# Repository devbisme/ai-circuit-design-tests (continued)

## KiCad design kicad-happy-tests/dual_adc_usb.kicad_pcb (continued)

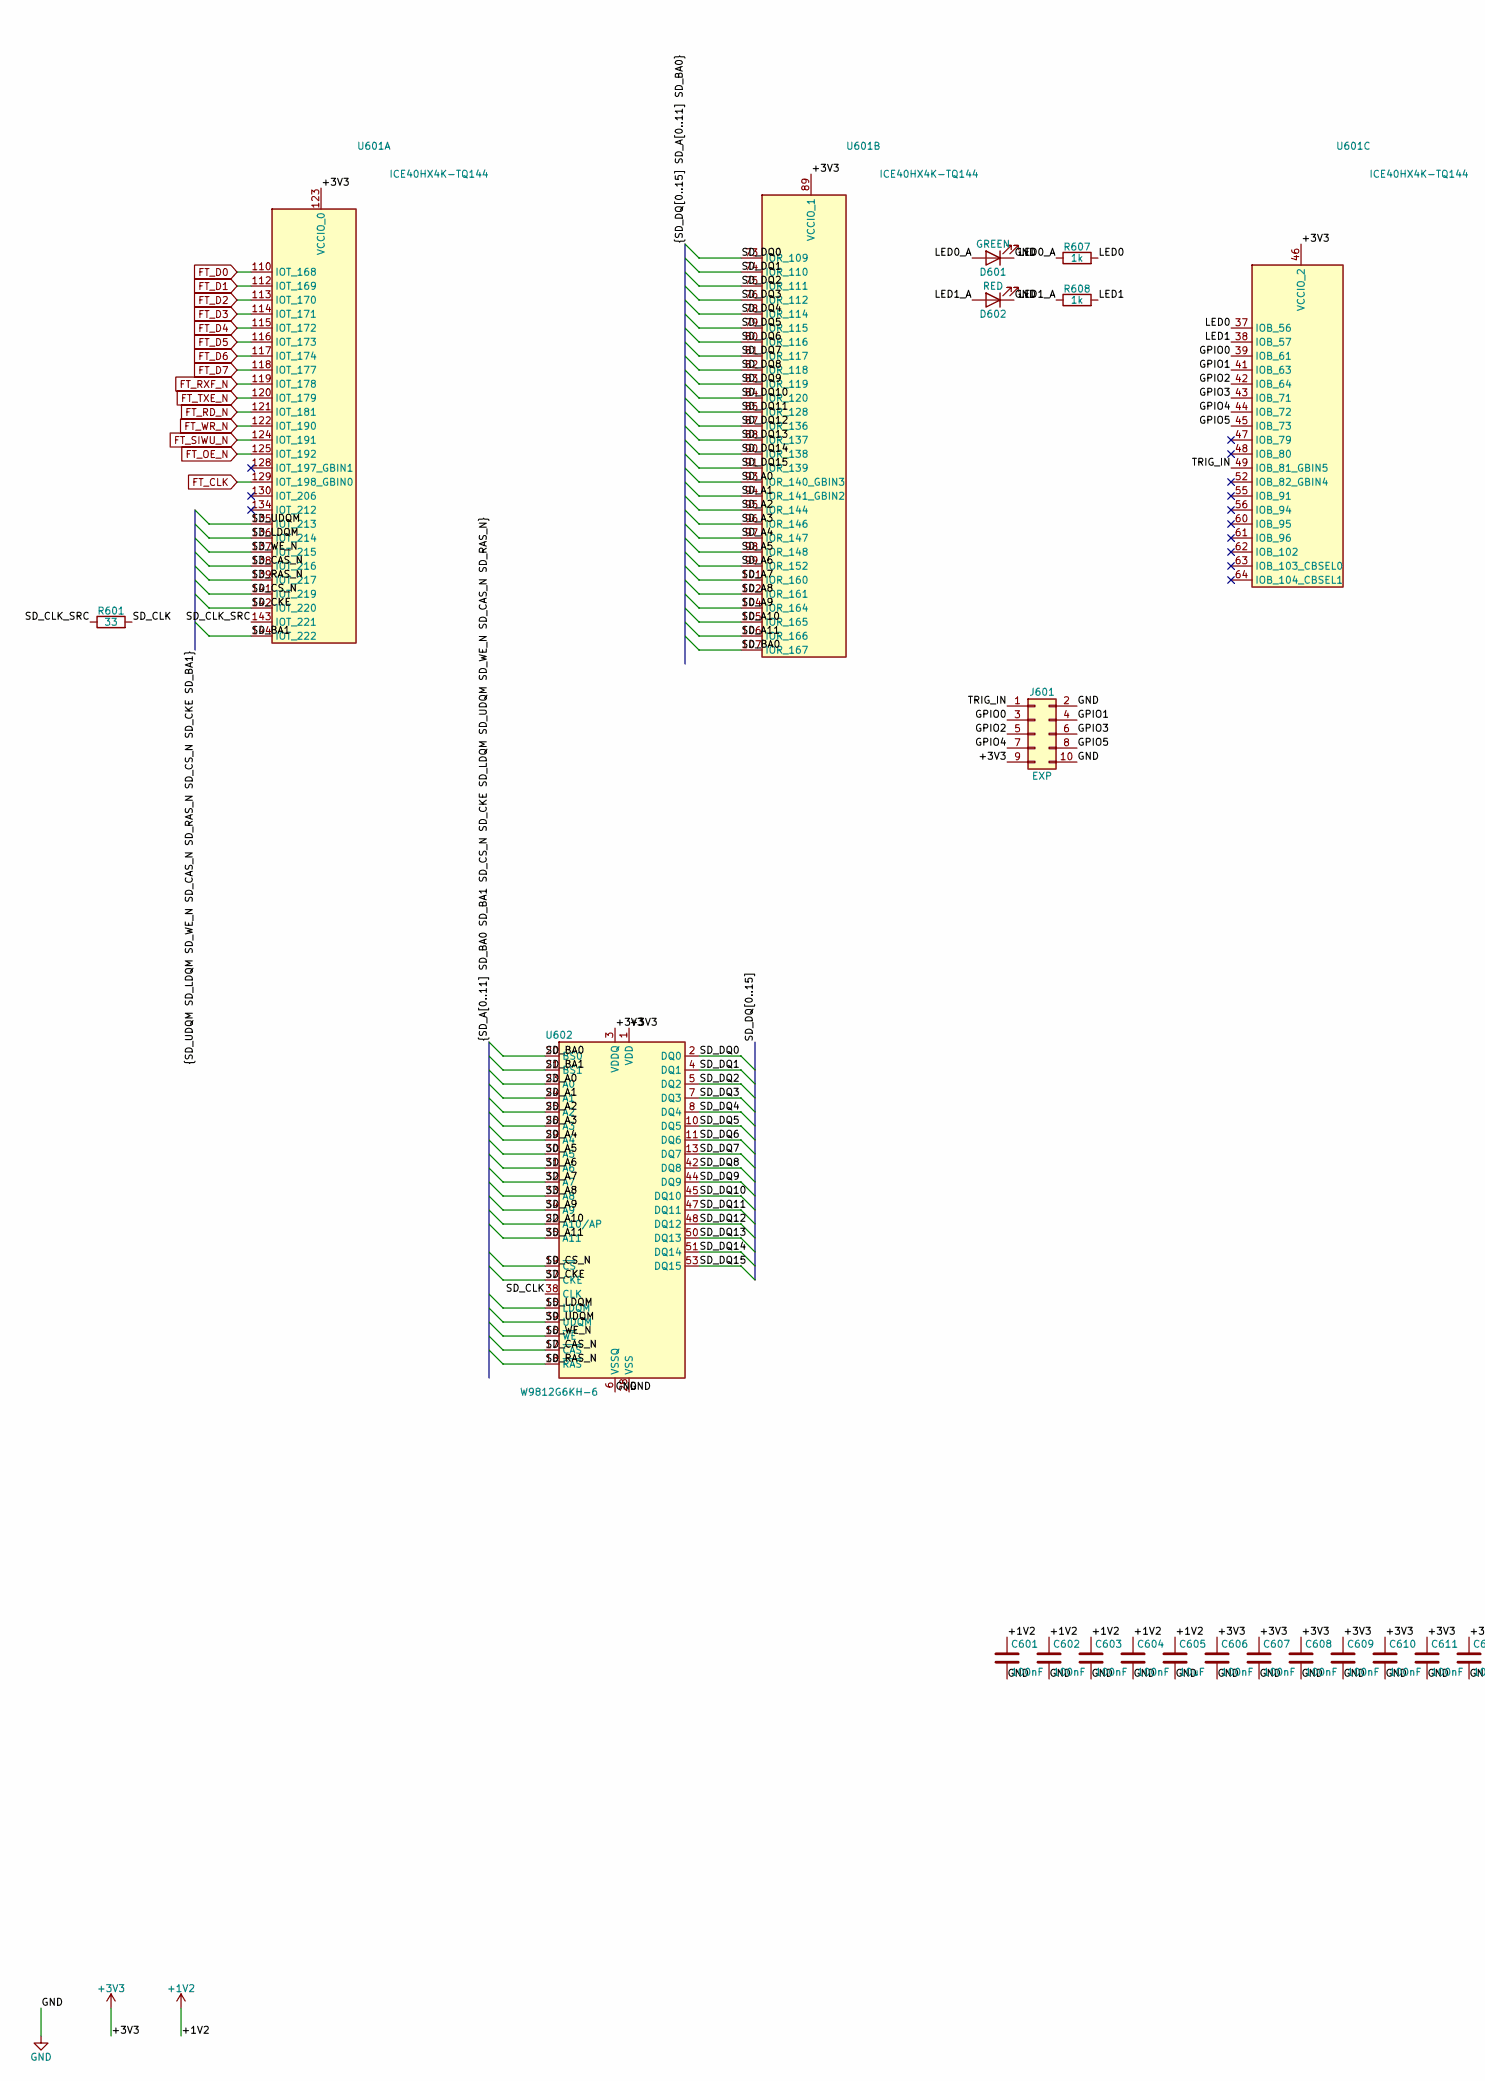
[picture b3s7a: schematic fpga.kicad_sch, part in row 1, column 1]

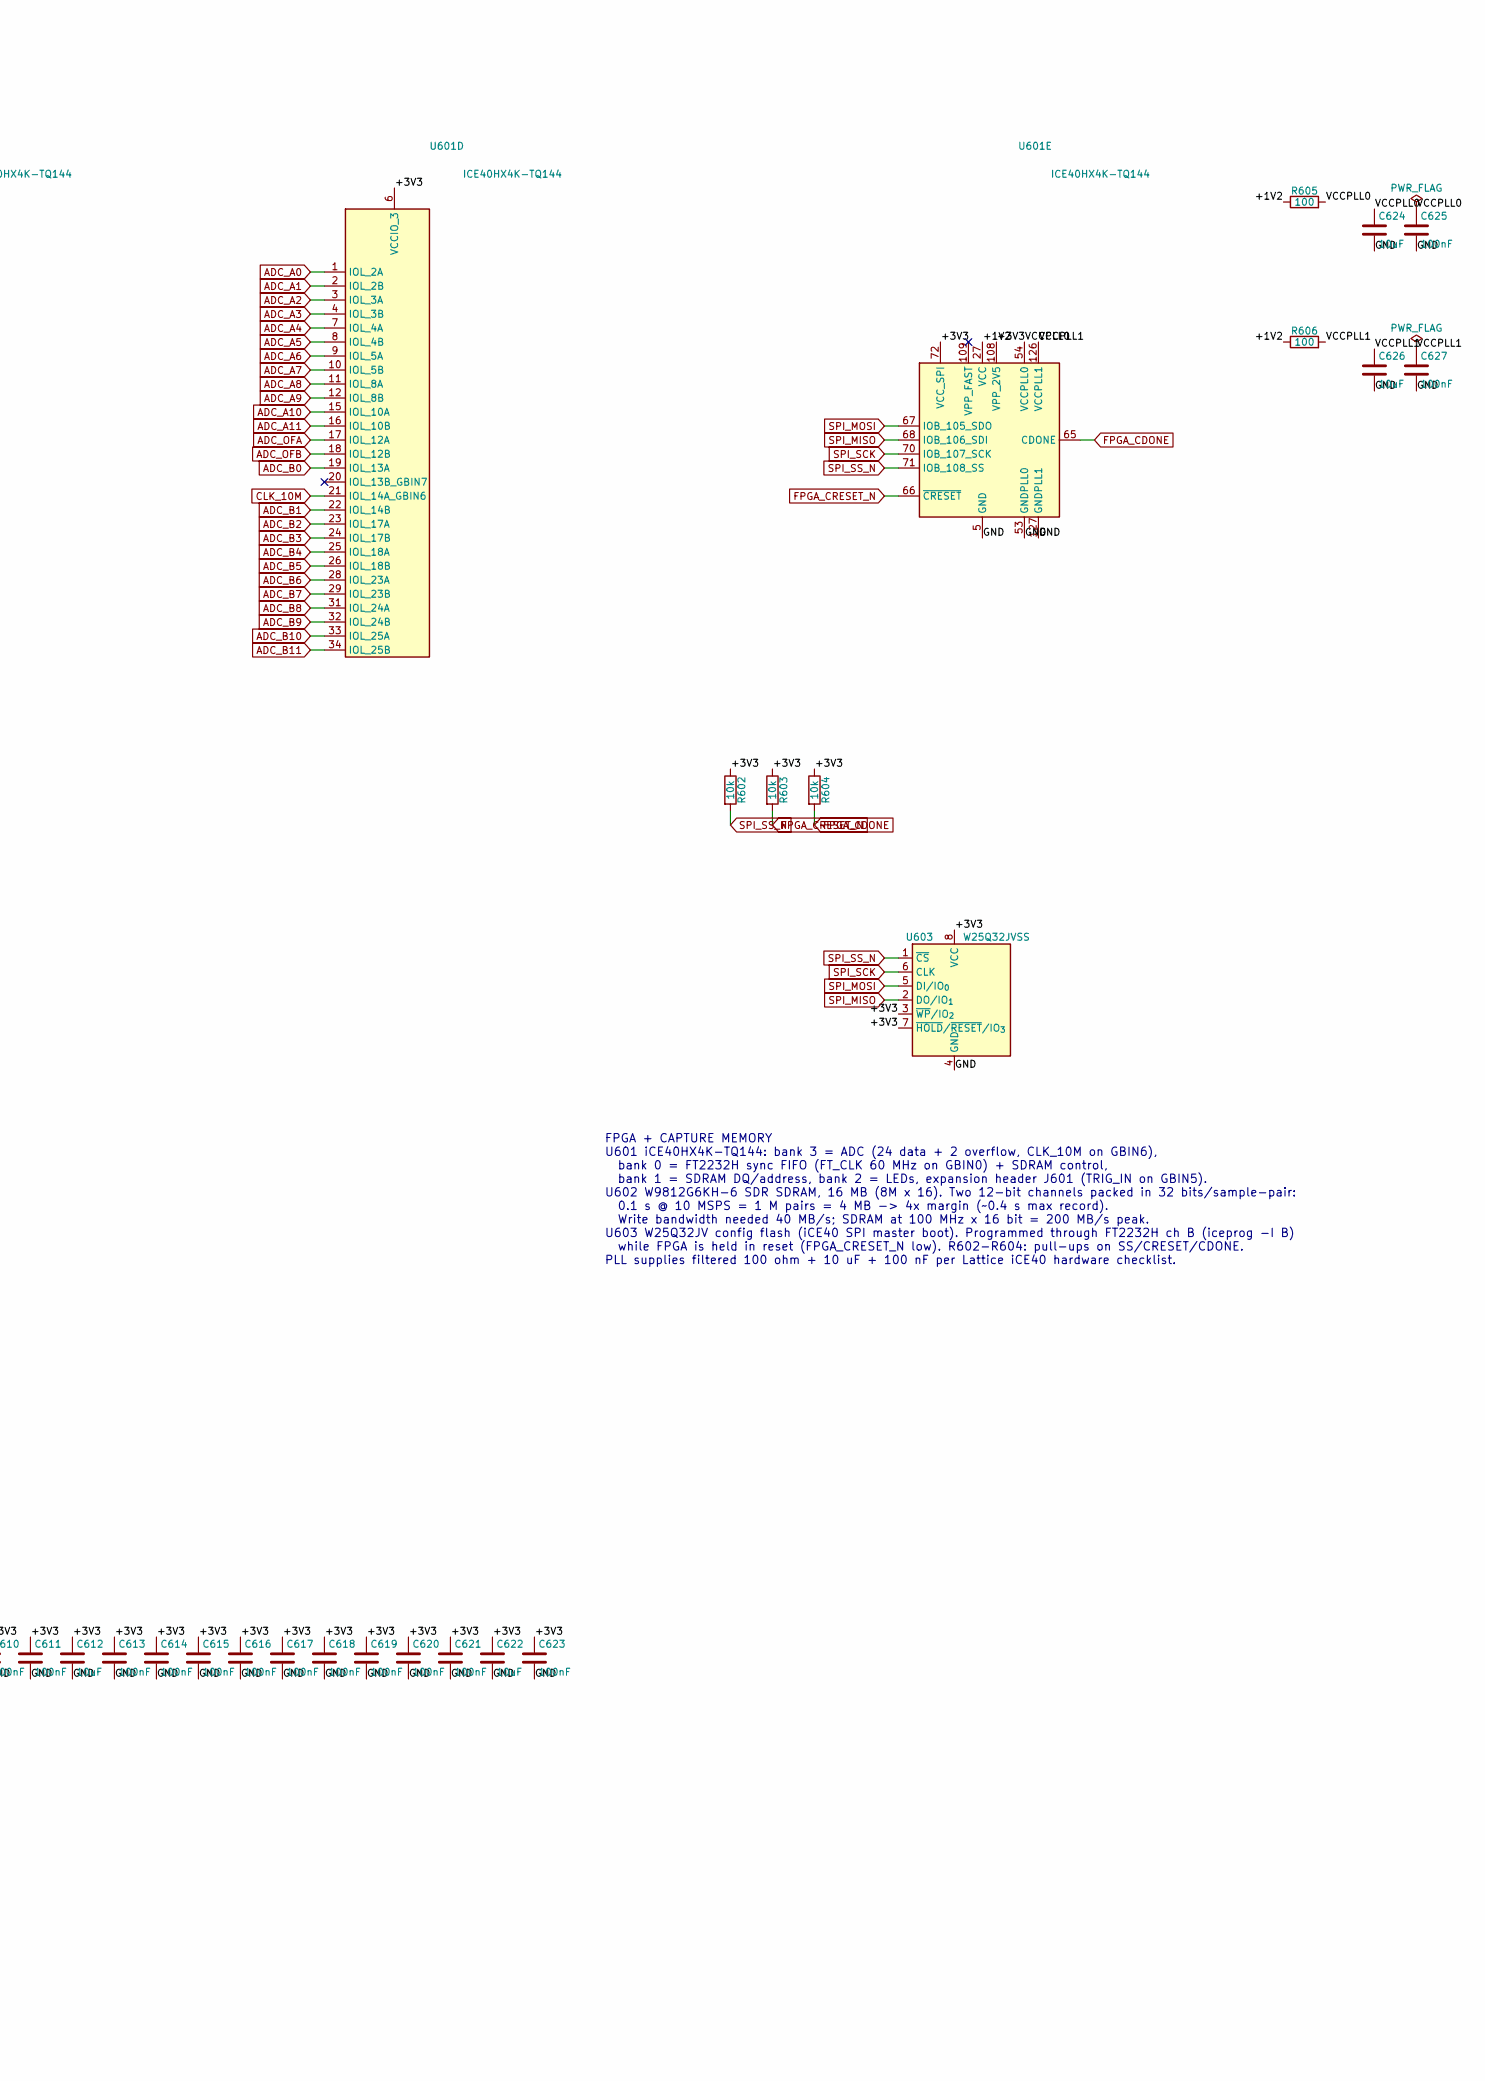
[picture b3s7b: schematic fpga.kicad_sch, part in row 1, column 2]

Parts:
C601, C602, C603, C604, C606, C607, C608, C609, C610, C611, C613, C614, C615, C616, C617, C618, C619, C620, C621, C623, C625, C627: 100nF; C_0402_1005Metric
C605, C612, C622, C624, C626: 10uF; C_0805_2012Metric
D601: GREEN; LED_0603_1608Metric
D602: RED; LED_0603_1608Metric
J601: EXP; PinHeader_2x05_P2.54mm_Vertical
R601: 33; R_0402_1005Metric
R602, R603, R604: 10k; R_0402_1005Metric
R605, R606: 100; R_0402_1005Metric
R607, R608: 1k; R_0402_1005Metric
U601: ICE40HX4K-TQ144; TQFP-144_20x20mm_P0.5mm
U602: W9812G6KH-6; TSOP-II-54_22.2x10.16mm_P0.8mm
U603: W25Q32JVSS; SOIC-8_5.3x5.3mm_P1.27mm

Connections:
+1V2: C601.1, C602.1, C603.1, C604.1, C605.1, R605.1, R606.1, U601.27 (VCC), U601.40 (VCC), U601.92 (VCC), U601.111 (VCC); also elsewhere on the board
+3V3: C606.1, C607.1, C608.1, C609.1, C610.1, C611.1, C612.1, C613.1, C614.1, C615.1, C616.1, C617.1, C618.1, C619.1, C620.1, C621.1, C622.1, C623.1, J601.9, R602.1, R603.1, R604.1, U601.6 (VCCIO_3), U601.30 (VCCIO_3), U601.46 (VCCIO_2), U601.57 (VCCIO_2), U601.72 (VCC_SPI), U601.89 (VCCIO_1), U601.100 (VCCIO_1), U601.108 (VPP_2V5), U601.123 (VCCIO_0), U601.131 (VCCIO_0), U602.1 (VDD), U602.3 (VDDQ), U602.9 (VDDQ), U602.14 (VDD), U602.27 (VDD), U602.43 (VDDQ), U602.49 (VDDQ), U603.3 (~WP/IO_{2}), U603.7 (~HOLD/~RESET/IO_{3}), U603.8 (VCC); also elsewhere on the board
/FPGA_SDRAM/GPIO0: J601.3, U601.39 (IOB_61)
/FPGA_SDRAM/GPIO1: J601.4, U601.41 (IOB_63)
/FPGA_SDRAM/GPIO2: J601.5, U601.42 (IOB_64)
/FPGA_SDRAM/GPIO3: J601.6, U601.43 (IOB_71)
/FPGA_SDRAM/GPIO4: J601.7, U601.44 (IOB_72)
/FPGA_SDRAM/GPIO5: J601.8, U601.45 (IOB_73)
/FPGA_SDRAM/LED0: R607.2, U601.37 (IOB_56)
/FPGA_SDRAM/LED0_A: D601.2 (A), R607.1
/FPGA_SDRAM/LED1: R608.2, U601.38 (IOB_57)
/FPGA_SDRAM/LED1_A: D602.2 (A), R608.1
/FPGA_SDRAM/SD_A0: U601.93 (IOR_140_GBIN3), U602.23 (A0)
/FPGA_SDRAM/SD_A1: U601.94 (IOR_141_GBIN2), U602.24 (A1)
/FPGA_SDRAM/SD_A2: U601.95 (IOR_144), U602.25 (A2)
/FPGA_SDRAM/SD_A3: U601.96 (IOR_146), U602.26 (A3)
/FPGA_SDRAM/SD_A4: U601.97 (IOR_147), U602.29 (A4)
/FPGA_SDRAM/SD_A5: U601.98 (IOR_148), U602.30 (A5)
/FPGA_SDRAM/SD_A6: U601.99 (IOR_152), U602.31 (A6)
/FPGA_SDRAM/SD_A7: U601.101 (IOR_160), U602.32 (A7)
/FPGA_SDRAM/SD_A8: U601.102 (IOR_161), U602.33 (A8)
/FPGA_SDRAM/SD_A9: U601.104 (IOR_164), U602.34 (A9)
/FPGA_SDRAM/SD_A10: U601.105 (IOR_165), U602.22 (A10/AP)
/FPGA_SDRAM/SD_A11: U601.106 (IOR_166), U602.35 (A11)
/FPGA_SDRAM/SD_BA0: U601.107 (IOR_167), U602.20 (BS0)
/FPGA_SDRAM/SD_BA1: U601.144 (IOT_222), U602.21 (BS1)
/FPGA_SDRAM/SD_CAS_N: U601.138 (IOT_216), U602.17 (~CAS)
/FPGA_SDRAM/SD_CKE: U601.142 (IOT_220), U602.37 (CKE)
/FPGA_SDRAM/SD_CLK: R601.2, U602.38 (CLK)
/FPGA_SDRAM/SD_CLK_SRC: R601.1, U601.143 (IOT_221)
/FPGA_SDRAM/SD_CS_N: U601.141 (IOT_219), U602.19 (~CS)
/FPGA_SDRAM/SD_DQ0: U601.73 (IOR_109), U602.2 (DQ0)
/FPGA_SDRAM/SD_DQ1: U601.74 (IOR_110), U602.4 (DQ1)
/FPGA_SDRAM/SD_DQ2: U601.75 (IOR_111), U602.5 (DQ2)
/FPGA_SDRAM/SD_DQ3: U601.76 (IOR_112), U602.7 (DQ3)
/FPGA_SDRAM/SD_DQ4: U601.78 (IOR_114), U602.8 (DQ4)
/FPGA_SDRAM/SD_DQ5: U601.79 (IOR_115), U602.10 (DQ5)
/FPGA_SDRAM/SD_DQ6: U601.80 (IOR_116), U602.11 (DQ6)
/FPGA_SDRAM/SD_DQ7: U601.81 (IOR_117), U602.13 (DQ7)
/FPGA_SDRAM/SD_DQ8: U601.82 (IOR_118), U602.42 (DQ8)
/FPGA_SDRAM/SD_DQ9: U601.83 (IOR_119), U602.44 (DQ9)
/FPGA_SDRAM/SD_DQ10: U601.84 (IOR_120), U602.45 (DQ10)
/FPGA_SDRAM/SD_DQ11: U601.85 (IOR_128), U602.47 (DQ11)
/FPGA_SDRAM/SD_DQ12: U601.87 (IOR_136), U602.48 (DQ12)
/FPGA_SDRAM/SD_DQ13: U601.88 (IOR_137), U602.50 (DQ13)
/FPGA_SDRAM/SD_DQ14: U601.90 (IOR_138), U602.51 (DQ14)
/FPGA_SDRAM/SD_DQ15: U601.91 (IOR_139), U602.53 (DQ15)
/FPGA_SDRAM/SD_LDQM: U601.136 (IOT_214), U602.15 (LDQM)
/FPGA_SDRAM/SD_RAS_N: U601.139 (IOT_217), U602.18 (~RAS)
/FPGA_SDRAM/SD_UDQM: U601.135 (IOT_213), U602.39 (UDQM)
/FPGA_SDRAM/SD_WE_N: U601.137 (IOT_215), U602.16 (~WE)
/FPGA_SDRAM/TRIG_IN: J601.1, U601.49 (IOB_81_GBIN5)
ADC_A0: U601.1 (IOL_2A); also elsewhere on the board
ADC_A1: U601.2 (IOL_2B); also elsewhere on the board
ADC_A2: U601.3 (IOL_3A); also elsewhere on the board
ADC_A3: U601.4 (IOL_3B); also elsewhere on the board
ADC_A4: U601.7 (IOL_4A); also elsewhere on the board
ADC_A5: U601.8 (IOL_4B); also elsewhere on the board
ADC_A6: U601.9 (IOL_5A); also elsewhere on the board
ADC_A7: U601.10 (IOL_5B); also elsewhere on the board
ADC_A8: U601.11 (IOL_8A); also elsewhere on the board
ADC_A9: U601.12 (IOL_8B); also elsewhere on the board
ADC_A10: U601.15 (IOL_10A); also elsewhere on the board
ADC_A11: U601.16 (IOL_10B); also elsewhere on the board
ADC_B0: U601.19 (IOL_13A); also elsewhere on the board
ADC_B1: U601.22 (IOL_14B); also elsewhere on the board
ADC_B2: U601.23 (IOL_17A); also elsewhere on the board
ADC_B3: U601.24 (IOL_17B); also elsewhere on the board
ADC_B4: U601.25 (IOL_18A); also elsewhere on the board
ADC_B5: U601.26 (IOL_18B); also elsewhere on the board
ADC_B6: U601.28 (IOL_23A); also elsewhere on the board
ADC_B7: U601.29 (IOL_23B); also elsewhere on the board
ADC_B8: U601.31 (IOL_24A); also elsewhere on the board
ADC_B9: U601.32 (IOL_24B); also elsewhere on the board
ADC_B10: U601.33 (IOL_25A); also elsewhere on the board
ADC_B11: U601.34 (IOL_25B); also elsewhere on the board
ADC_OFA: U601.17 (IOL_12A); also elsewhere on the board
ADC_OFB: U601.18 (IOL_12B); also elsewhere on the board
CLK_10M: U601.21 (IOL_14A_GBIN6); also elsewhere on the board
FPGA_CDONE: R604.2, U601.65 (CDONE); also elsewhere on the board
FPGA_CRESET_N: R603.2, U601.66 (~CRESET); also elsewhere on the board
FT_CLK: U601.129 (IOT_198_GBIN0); also elsewhere on the board
FT_D0: U601.110 (IOT_168); also elsewhere on the board
FT_D1: U601.112 (IOT_169); also elsewhere on the board
FT_D2: U601.113 (IOT_170); also elsewhere on the board
FT_D3: U601.114 (IOT_171); also elsewhere on the board
FT_D4: U601.115 (IOT_172); also elsewhere on the board
FT_D5: U601.116 (IOT_173); also elsewhere on the board
FT_D6: U601.117 (IOT_174); also elsewhere on the board
FT_D7: U601.118 (IOT_177); also elsewhere on the board
FT_OE_N: U601.125 (IOT_192); also elsewhere on the board
FT_RD_N: U601.121 (IOT_181); also elsewhere on the board
FT_RXF_N: U601.119 (IOT_178); also elsewhere on the board
FT_SIWU_N: U601.124 (IOT_191); also elsewhere on the board
FT_TXE_N: U601.120 (IOT_179); also elsewhere on the board
FT_WR_N: U601.122 (IOT_190); also elsewhere on the board
GND: C601.2, C602.2, C603.2, C604.2, C605.2, C606.2, C607.2, C608.2, C609.2, C610.2, C611.2, C612.2, C613.2, C614.2, C615.2, C616.2, C617.2, C618.2, C619.2, C620.2, C621.2, C622.2, C623.2, C624.2, C625.2, C626.2, C627.2, D601.1 (K), D602.1 (K), J601.2, J601.10, U601.5 (GND), U601.13 (GND), U601.14 (GND), U601.53 (GNDPLL0), U601.59 (GND), U601.69 (GND), U601.86 (GND), U601.103 (GND), U601.127 (GNDPLL1), U601.132 (GND), U601.140 (GND), U602.6 (VSSQ), U602.12 (VSSQ), U602.28 (VSS), U602.41 (VSS), U602.46 (VSSQ), U602.52 (VSSQ), U602.54 (VSS), U603.4 (GND); also elsewhere on the board
SPI_MISO: U601.68 (IOB_106_SDI), U603.2 (DO/IO_{1}); also elsewhere on the board
SPI_MOSI: U601.67 (IOB_105_SDO), U603.5 (DI/IO_{0}); also elsewhere on the board
SPI_SCK: U601.70 (IOB_107_SCK), U603.6 (CLK); also elsewhere on the board
SPI_SS_N: R602.2, U601.71 (IOB_108_SS), U603.1 (~CS); also elsewhere on the board

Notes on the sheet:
FPGA + CAPTURE MEMORY U601 iCE40HX4K-TQ144: bank 3 = ADC (24 data + 2 overflow, CLK_10M on GBIN6), bank 0 = FT2232H sync FIFO (FT_CLK 60 MHz on GBIN0) + SDRAM control, bank 1 = SDRAM DQ/address, bank 2 = LEDs, expansion header J601 (TRIG_IN on GBIN5). U602 W9812G6KH-6 SDR SDRAM, 16 MB (8M x 16). Tw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

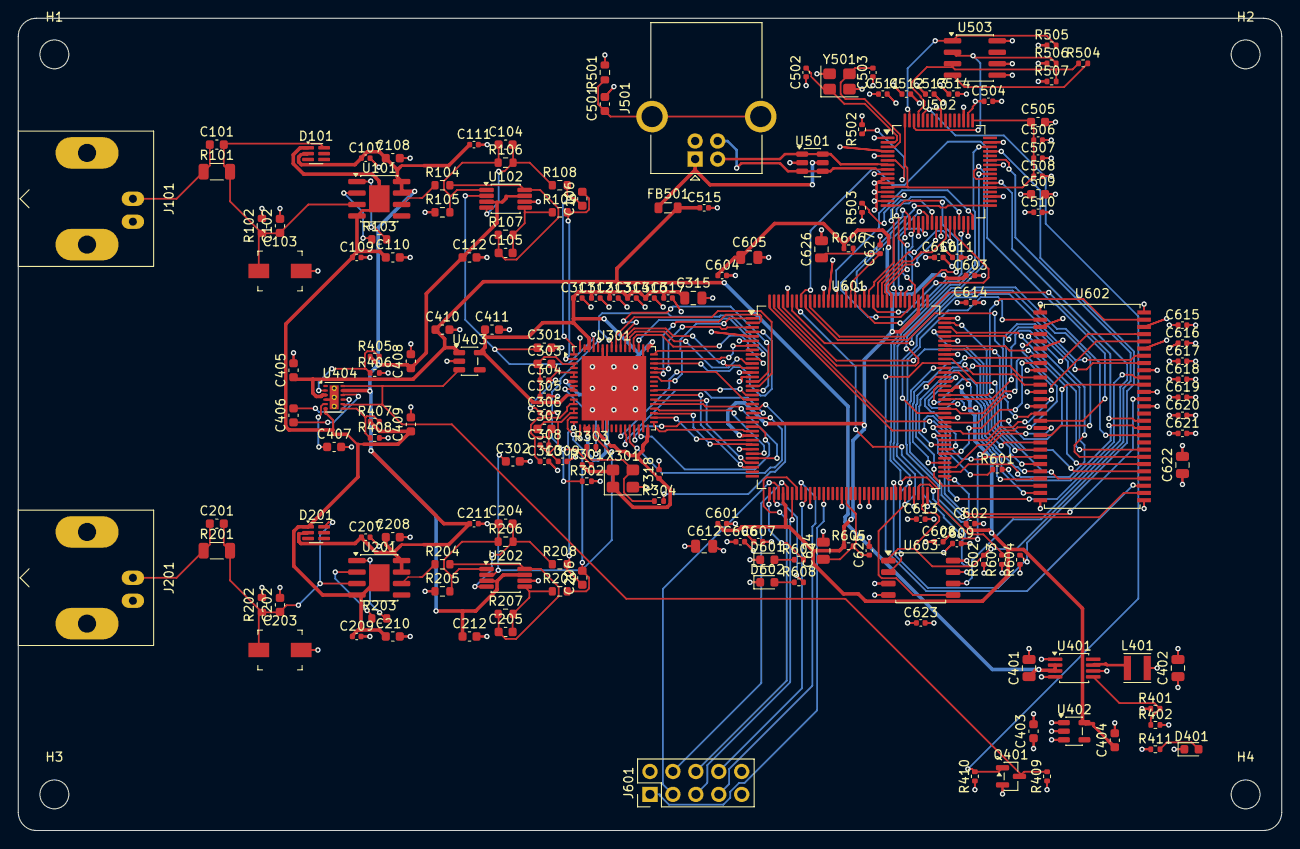
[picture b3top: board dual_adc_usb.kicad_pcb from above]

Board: 4 copper layers, 140.0 x 90.0 mm, 174 parts (0 on the bottom side), 161 nets.

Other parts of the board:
H1, H2, H3, H4: MountingHole_3.2mm_M3

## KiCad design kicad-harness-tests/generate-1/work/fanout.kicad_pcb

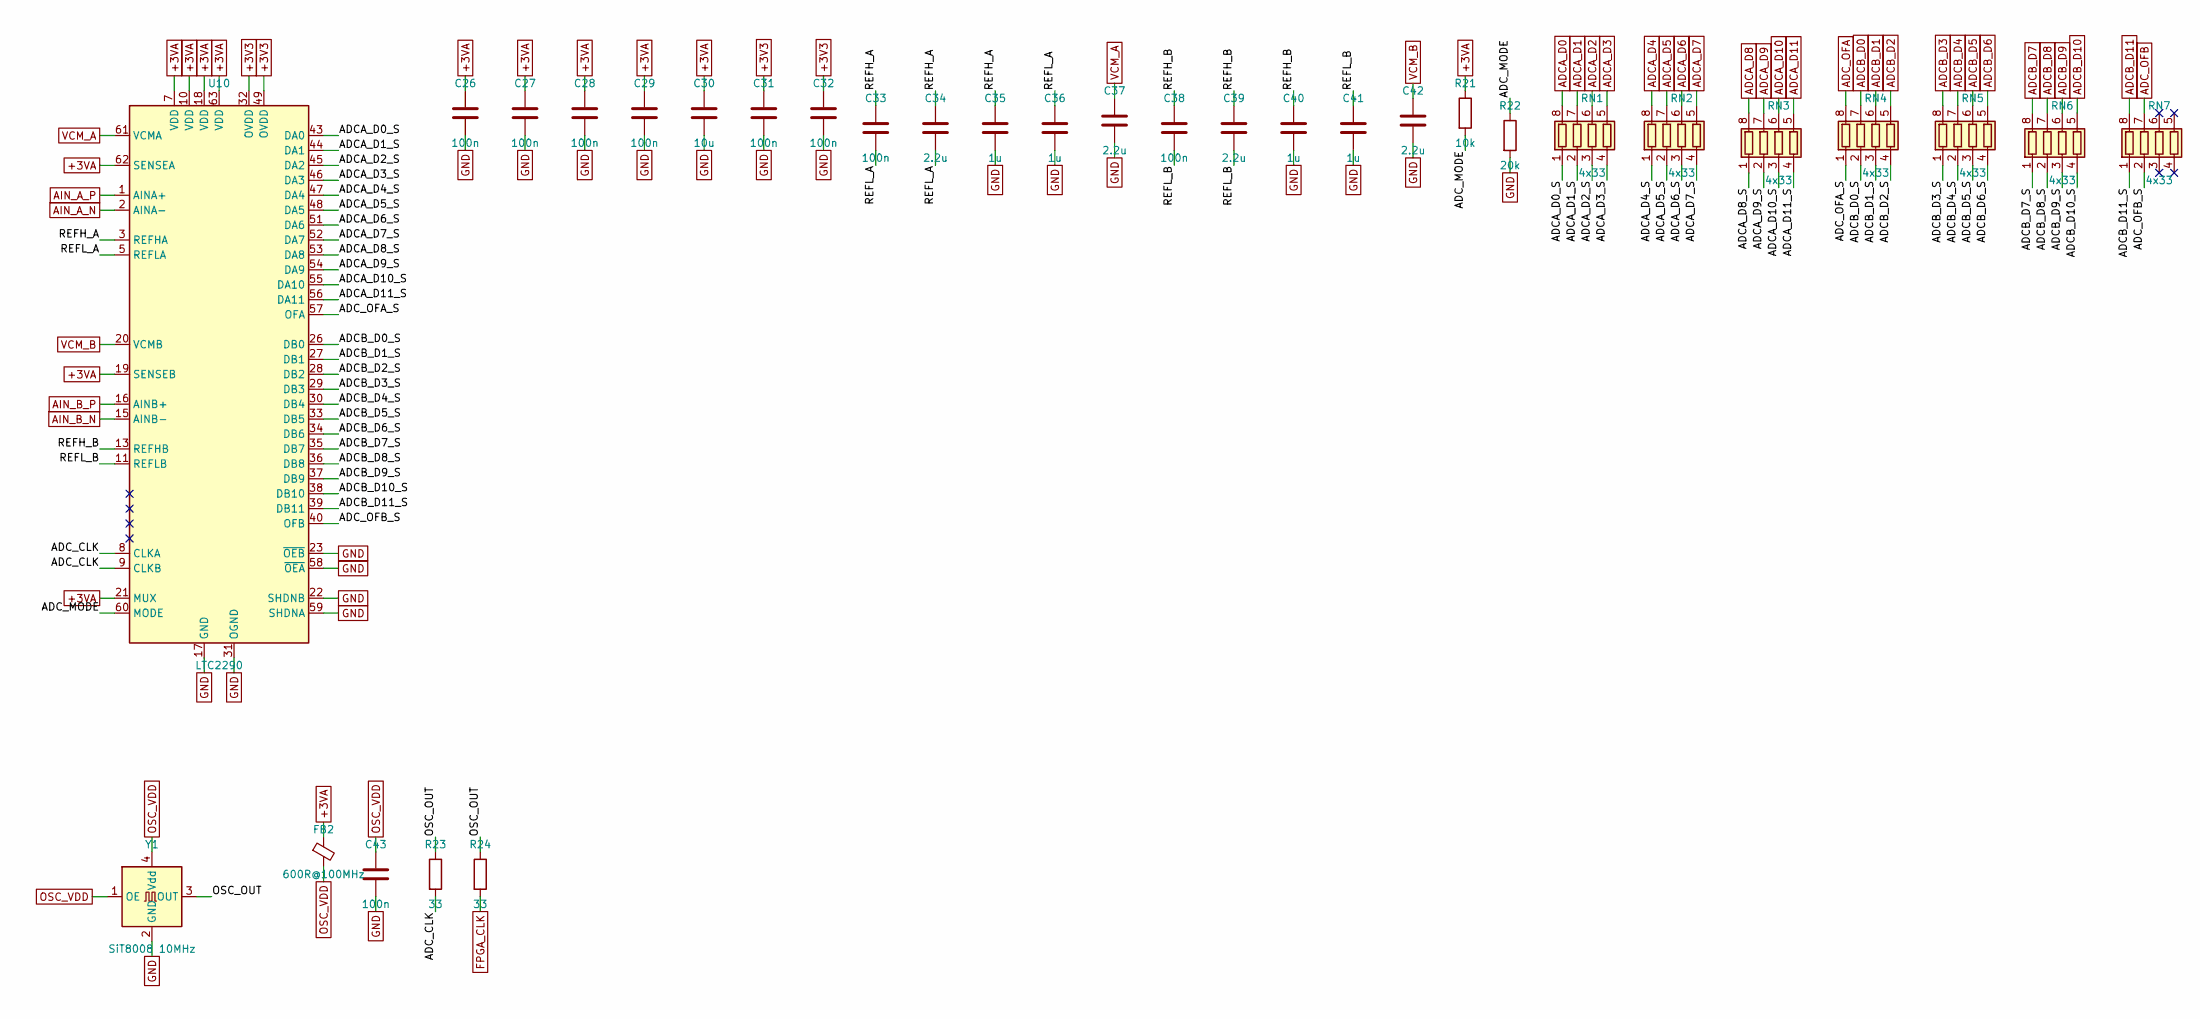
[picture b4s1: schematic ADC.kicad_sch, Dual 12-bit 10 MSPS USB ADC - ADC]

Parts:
C26, C27, C28, C29, C31, C32, C33, C38, C43: 100n; C_0603_1608Metric
C30: 10u; C_0805_2012Metric
C34, C37, C39, C42: 2.2u; C_0603_1608Metric
C35, C36, C40, C41: 1u; C_0603_1608Metric
FB2: 600R@100MHz; L_0805_2012Metric
R21: 10k; R_0603_1608Metric
R22: 20k; R_0603_1608Metric
R23, R24: 33; R_0603_1608Metric
RN1, RN2, RN3, RN4, RN5, RN6, RN7: 4x33; R_Array_Convex_4x0603
U10: LTC2290; QFN-64-1EP_9x9mm_P0.5mm_EP7.15x7.15mm
Y1: SiT8008 10MHz; Oscillator_SMD_SiT_PQFN-4Pin_3.2x2.5mm

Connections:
+3V3: C31.1, C32.1, U10.32 (OVDD), U10.49 (OVDD); also elsewhere on the board
+3VA: C26.1, C27.1, C28.1, C29.1, C30.1, FB2.1, R21.1, U10.7 (VDD), U10.10 (VDD), U10.18 (VDD), U10.19 (SENSEB), U10.21 (MUX), U10.62 (SENSEA), U10.63 (VDD); also elsewhere on the board
/ADC/ADCA_D0_S: RN1.1 (R1.1), U10.43 (DA0)
/ADC/ADCA_D1_S: RN1.2 (R2.1), U10.44 (DA1)
/ADC/ADCA_D2_S: RN1.3 (R3.1), U10.45 (DA2)
/ADC/ADCA_D3_S: RN1.4 (R4.1), U10.46 (DA3)
/ADC/ADCA_D4_S: RN2.1 (R1.1), U10.47 (DA4)
/ADC/ADCA_D5_S: RN2.2 (R2.1), U10.48 (DA5)
/ADC/ADCA_D6_S: RN2.3 (R3.1), U10.51 (DA6)
/ADC/ADCA_D7_S: RN2.4 (R4.1), U10.52 (DA7)
/ADC/ADCA_D8_S: RN3.1 (R1.1), U10.53 (DA8)
/ADC/ADCA_D9_S: RN3.2 (R2.1), U10.54 (DA9)
/ADC/ADCA_D10_S: RN3.3 (R3.1), U10.55 (DA10)
/ADC/ADCA_D11_S: RN3.4 (R4.1), U10.56 (DA11)
/ADC/ADCB_D0_S: RN4.2 (R2.1), U10.26 (DB0)
/ADC/ADCB_D1_S: RN4.3 (R3.1), U10.27 (DB1)
/ADC/ADCB_D2_S: RN4.4 (R4.1), U10.28 (DB2)
/ADC/ADCB_D3_S: RN5.1 (R1.1), U10.29 (DB3)
/ADC/ADCB_D4_S: RN5.2 (R2.1), U10.30 (DB4)
/ADC/ADCB_D5_S: RN5.3 (R3.1), U10.33 (DB5)
/ADC/ADCB_D6_S: RN5.4 (R4.1), U10.34 (DB6)
/ADC/ADCB_D7_S: RN6.1 (R1.1), U10.35 (DB7)
/ADC/ADCB_D8_S: RN6.2 (R2.1), U10.36 (DB8)
/ADC/ADCB_D9_S: RN6.3 (R3.1), U10.37 (DB9)
/ADC/ADCB_D10_S: RN6.4 (R4.1), U10.38 (DB10)
/ADC/ADCB_D11_S: RN7.1 (R1.1), U10.39 (DB11)
/ADC/ADC_CLK: R23.2, U10.8 (CLKA), U10.9 (CLKB)
/ADC/ADC_MODE: R21.2, R22.1, U10.60 (MODE)
/ADC/ADC_OFA_S: RN4.1 (R1.1), U10.57 (OFA)
/ADC/ADC_OFB_S: RN7.2 (R2.1), U10.40 (OFB)
/ADC/OSC_OUT: R23.1, R24.1, Y1.3 (OUT)
/ADC/REFH_A: C33.1, C34.1, C35.1, U10.3 (REFHA), U10.4 (REFHA)
/ADC/REFH_B: C38.1, C39.1, C40.1, U10.13 (REFHB), U10.14 (REFHB)
/ADC/REFL_A: C33.2, C34.2, C36.1, U10.5 (REFLA), U10.6 (REFLA)
/ADC/REFL_B: C38.2, C39.2, C41.1, U10.11 (REFLB), U10.12 (REFLB)
ADCA_D0: RN1.8 (R1.2); also elsewhere on the board
ADCA_D1: RN1.7 (R2.2); also elsewhere on the board
ADCA_D2: RN1.6 (R3.2); also elsewhere on the board
ADCA_D3: RN1.5 (R4.2); also elsewhere on the board
ADCA_D4: RN2.8 (R1.2); also elsewhere on the board
ADCA_D5: RN2.7 (R2.2); also elsewhere on the board
ADCA_D6: RN2.6 (R3.2); also elsewhere on the board
ADCA_D7: RN2.5 (R4.2); also elsewhere on the board
ADCA_D8: RN3.8 (R1.2); also elsewhere on the board
ADCA_D9: RN3.7 (R2.2); also elsewhere on the board
ADCA_D10: RN3.6 (R3.2); also elsewhere on the board
ADCA_D11: RN3.5 (R4.2); also elsewhere on the board
ADCB_D0: RN4.7 (R2.2); also elsewhere on the board
ADCB_D1: RN4.6 (R3.2); also elsewhere on the board
ADCB_D2: RN4.5 (R4.2); also elsewhere on the board
ADCB_D3: RN5.8 (R1.2); also elsewhere on the board
ADCB_D4: RN5.7 (R2.2); also elsewhere on the board
ADCB_D5: RN5.6 (R3.2); also elsewhere on the board
ADCB_D6: RN5.5 (R4.2); also elsewhere on the board
ADCB_D7: RN6.8 (R1.2); also elsewhere on the board
ADCB_D8: RN6.7 (R2.2); also elsewhere on the board
ADCB_D9: RN6.6 (R3.2); also elsewhere on the board
ADCB_D10: RN6.5 (R4.2); also elsewhere on the board
ADCB_D11: RN7.8 (R1.2); also elsewhere on the board
ADC_OFA: RN4.8 (R1.2); also elsewhere on the board
ADC_OFB: RN7.7 (R2.2); also elsewhere on the board
AIN_A_N: U10.2 (AINA-); also elsewhere on the board
AIN_A_P: U10.1 (AINA+); also elsewhere on the board
AIN_B_N: U10.15 (AINB-); also elsewhere on the board
AIN_B_P: U10.16 (AINB+); also elsewhere on the board
FPGA_CLK: R24.2; also elsewhere on the board
GND: C26.2, C27.2, C28.2, C29.2, C30.2, C31.2, C32.2, C35.2, C36.2, C37.2, C40.2, C41.2, C42.2, C43.2, R22.2, U10.17 (GND), U10.22 (SHDNB), U10.23 (~OEB), U10.31 (OGND), U10.50 (OGND), U10.58 (~OEA), U10.59 (SHDNA), U10.64 (GND), U10.65 (GND), Y1.2 (GND); also elsewhere on the board
OSC_VDD: C43.1, FB2.2, Y1.1 (OE), Y1.4 (Vdd)
VCM_A: C37.1, U10.61 (VCMA); also elsewhere on the board
VCM_B: C42.1, U10.20 (VCMB); also elsewhere on the board

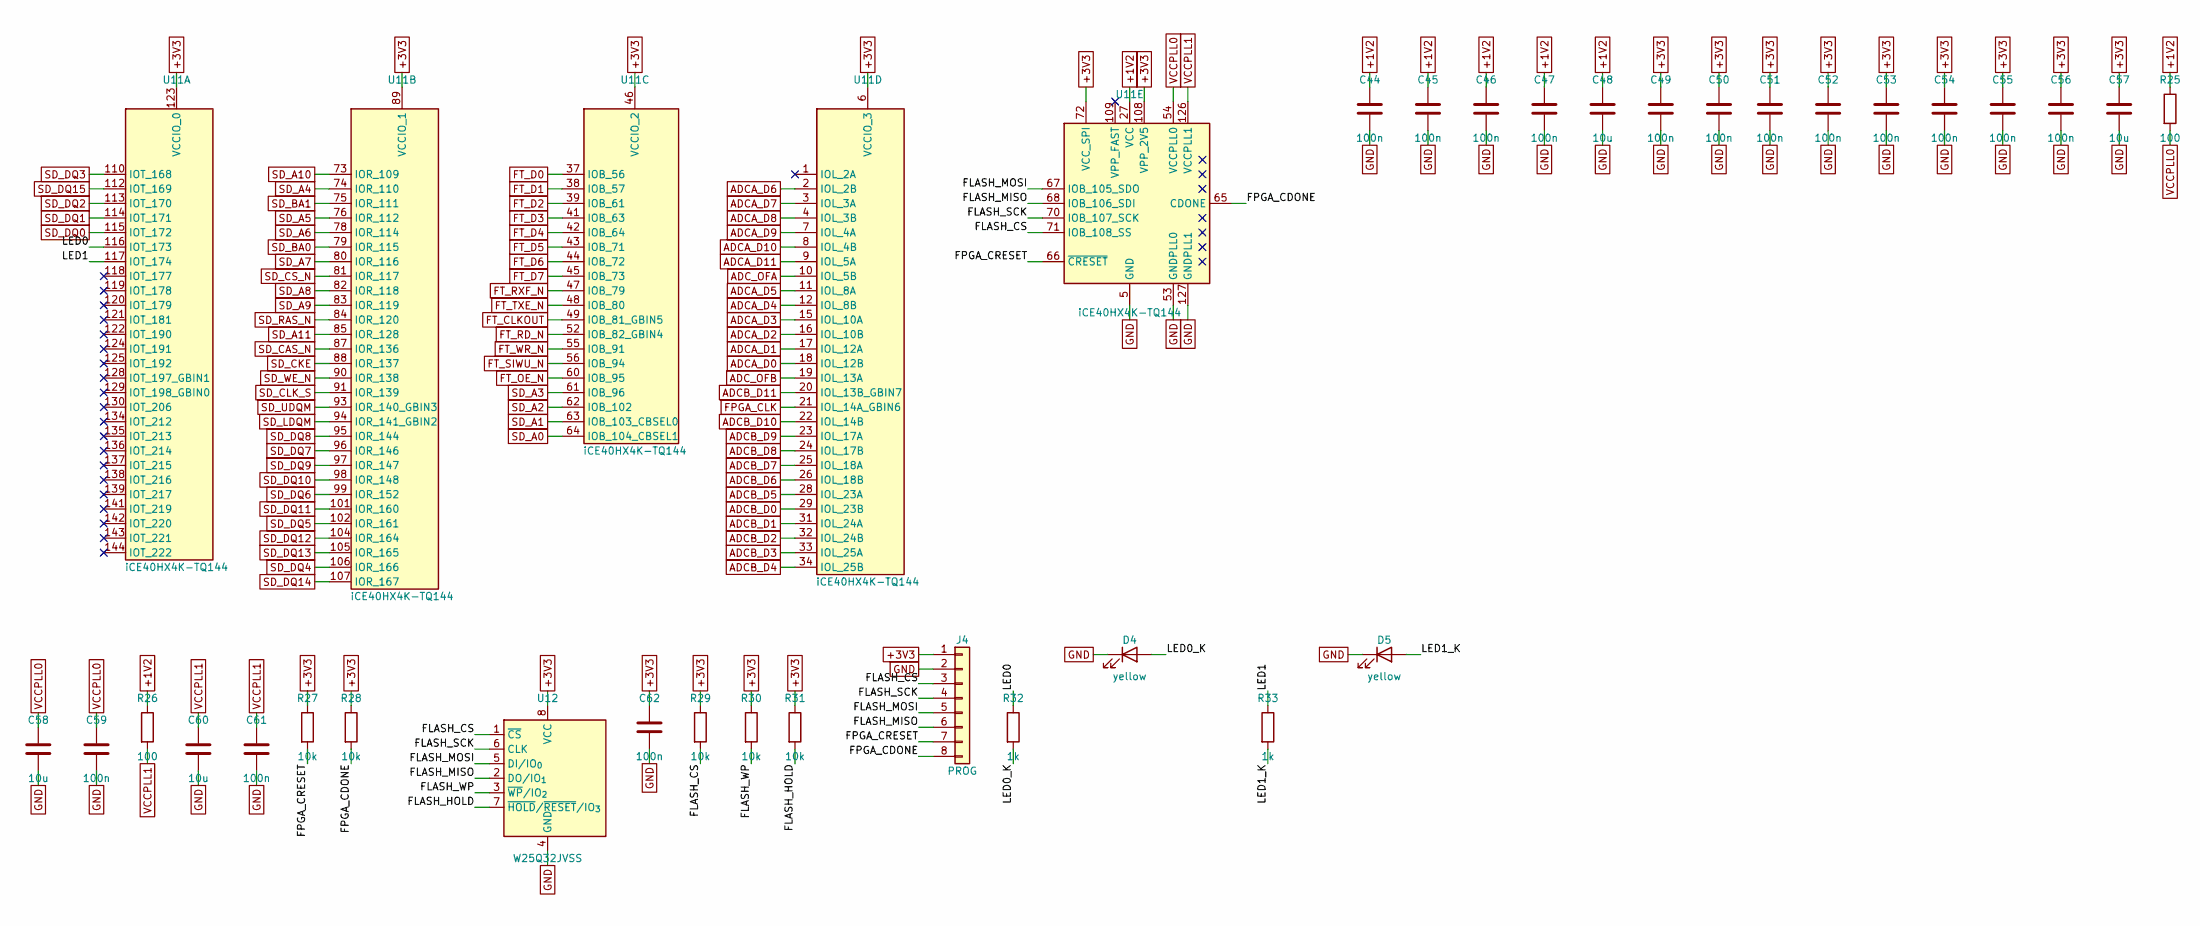
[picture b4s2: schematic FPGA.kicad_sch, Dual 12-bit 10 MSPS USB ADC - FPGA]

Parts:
C44, C45, C46, C47, C49, C50, C51, C52, C53, C54, C55, C56, C59, C61, C62: 100n; C_0603_1608Metric
C48, C57, C58, C60: 10u; C_0805_2012Metric
D4, D5: yellow; LED_0603_1608Metric
J4: PROG; PinHeader_1x08_P2.54mm_Vertical
R25, R26: 100; R_0603_1608Metric
R27, R28, R29, R30, R31: 10k; R_0603_1608Metric
R32, R33: 1k; R_0603_1608Metric
U11: iCE40HX4K-TQ144; TQFP-144_20x20mm_P0.5mm
U12: W25Q32JVSS; SOIC-8_5.3x5.3mm_P1.27mm

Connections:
+1V2: C44.1, C45.1, C46.1, C47.1, C48.1, R25.1, R26.1, U11.27 (VCC), U11.40 (VCC), U11.92 (VCC), U11.111 (VCC); also elsewhere on the board
+3V3: C49.1, C50.1, C51.1, C52.1, C53.1, C54.1, C55.1, C56.1, C57.1, C62.1, J4.1, R27.1, R28.1, R29.1, R30.1, R31.1, U11.6 (VCCIO_3), U11.30 (VCCIO_3), U11.46 (VCCIO_2), U11.57 (VCCIO_2), U11.72 (VCC_SPI), U11.89 (VCCIO_1), U11.100 (VCCIO_1), U11.108 (VPP_2V5), U11.123 (VCCIO_0), U11.131 (VCCIO_0), U12.8 (VCC); also elsewhere on the board
/FPGA/FLASH_CS: J4.3, R29.2, U11.71 (IOB_108_SS), U12.1 (~CS)
/FPGA/FLASH_HOLD: R31.2, U12.7 (~HOLD/~RESET/IO_{3})
/FPGA/FLASH_MISO: J4.6, U11.68 (IOB_106_SDI), U12.2 (DO/IO_{1})
/FPGA/FLASH_MOSI: J4.5, U11.67 (IOB_105_SDO), U12.5 (DI/IO_{0})
/FPGA/FLASH_SCK: J4.4, U11.70 (IOB_107_SCK), U12.6 (CLK)
/FPGA/FLASH_WP: R30.2, U12.3 (~WP/IO_{2})
/FPGA/FPGA_CDONE: J4.8, R28.2, U11.65 (CDONE)
/FPGA/FPGA_CRESET: J4.7, R27.2, U11.66 (~CRESET)
/FPGA/LED0: R32.1, U11.116 (IOT_173)
/FPGA/LED0_K: D4.2 (A), R32.2
/FPGA/LED1: R33.1, U11.117 (IOT_174)
/FPGA/LED1_K: D5.2 (A), R33.2
ADCA_D0: U11.18 (IOL_12B); also elsewhere on the board
ADCA_D1: U11.17 (IOL_12A); also elsewhere on the board
ADCA_D2: U11.16 (IOL_10B); also elsewhere on the board
ADCA_D3: U11.15 (IOL_10A); also elsewhere on the board
ADCA_D4: U11.12 (IOL_8B); also elsewhere on the board
ADCA_D5: U11.11 (IOL_8A); also elsewhere on the board
ADCA_D6: U11.2 (IOL_2B); also elsewhere on the board
ADCA_D7: U11.3 (IOL_3A); also elsewhere on the board
ADCA_D8: U11.4 (IOL_3B); also elsewhere on the board
ADCA_D9: U11.7 (IOL_4A); also elsewhere on the board
ADCA_D10: U11.8 (IOL_4B); also elsewhere on the board
ADCA_D11: U11.9 (IOL_5A); also elsewhere on the board
ADCB_D0: U11.29 (IOL_23B); also elsewhere on the board
ADCB_D1: U11.31 (IOL_24A); also elsewhere on the board
ADCB_D2: U11.32 (IOL_24B); also elsewhere on the board
ADCB_D3: U11.33 (IOL_25A); also elsewhere on the board
ADCB_D4: U11.34 (IOL_25B); also elsewhere on the board
ADCB_D5: U11.28 (IOL_23A); also elsewhere on the board
ADCB_D6: U11.26 (IOL_18B); also elsewhere on the board
ADCB_D7: U11.25 (IOL_18A); also elsewhere on the board
ADCB_D8: U11.24 (IOL_17B); also elsewhere on the board
ADCB_D9: U11.23 (IOL_17A); also elsewhere on the board
ADCB_D10: U11.22 (IOL_14B); also elsewhere on the board
ADCB_D11: U11.20 (IOL_13B_GBIN7); also elsewhere on the board
ADC_OFA: U11.10 (IOL_5B); also elsewhere on the board
ADC_OFB: U11.19 (IOL_13A); also elsewhere on the board
FPGA_CLK: U11.21 (IOL_14A_GBIN6); also elsewhere on the board
FT_CLKOUT: U11.49 (IOB_81_GBIN5); also elsewhere on the board
FT_D0: U11.37 (IOB_56); also elsewhere on the board
FT_D1: U11.38 (IOB_57); also elsewhere on the board
FT_D2: U11.39 (IOB_61); also elsewhere on the board
FT_D3: U11.41 (IOB_63); also elsewhere on the board
FT_D4: U11.42 (IOB_64); also elsewhere on the board
FT_D5: U11.43 (IOB_71); also elsewhere on the board
FT_D6: U11.44 (IOB_72); also elsewhere on the board
FT_D7: U11.45 (IOB_73); also elsewhere on the board
FT_OE_N: U11.60 (IOB_95); also elsewhere on the board
FT_RD_N: U11.52 (IOB_82_GBIN4); also elsewhere on the board
FT_RXF_N: U11.47 (IOB_79); also elsewhere on the board
FT_SIWU_N: U11.56 (IOB_94); also elsewhere on the board
FT_TXE_N: U11.48 (IOB_80); also elsewhere on the board
FT_WR_N: U11.55 (IOB_91); also elsewhere on the board
GND: C44.2, C45.2, C46.2, C47.2, C48.2, C49.2, C50.2, C51.2, C52.2, C53.2, C54.2, C55.2, C56.2, C57.2, C58.2, C59.2, C60.2, C61.2, C62.2, D4.1 (K), D5.1 (K), J4.2, U11.5 (GND), U11.13 (GND), U11.14 (GND), U11.53 (GNDPLL0), U11.59 (GND), U11.69 (GND), U11.86 (GND), U11.103 (GND), U11.127 (GNDPLL1), U11.132 (GND), U11.140 (GND), U12.4 (GND); also elsewhere on the board
SD_A0: U11.64 (IOB_104_CBSEL1); also elsewhere on the board
SD_A1: U11.63 (IOB_103_CBSEL0); also elsewhere on the board
SD_A2: U11.62 (IOB_102); also elsewhere on the board
SD_A3: U11.61 (IOB_96); also elsewhere on the board
SD_A4: U11.74 (IOR_110); also elsewhere on the board
SD_A5: U11.76 (IOR_112); also elsewhere on the board
SD_A6: U11.78 (IOR_114); also elsewhere on the board
SD_A7: U11.80 (IOR_116); also elsewhere on the board
SD_A8: U11.82 (IOR_118); also elsewhere on the board
SD_A9: U11.83 (IOR_119); also elsewhere on the board
SD_A10: U11.73 (IOR_109); also elsewhere on the board
SD_A11: U11.85 (IOR_128); also elsewhere on the board
SD_BA0: U11.79 (IOR_115); also elsewhere on the board
SD_BA1: U11.75 (IOR_111); also elsewhere on the board
SD_CAS_N: U11.87 (IOR_136); also elsewhere on the board
SD_CKE: U11.88 (IOR_137); also elsewhere on the board
SD_CLK_S: U11.91 (IOR_139); also elsewhere on the board
SD_CS_N: U11.81 (IOR_117); also elsewhere on the board
SD_DQ0: U11.115 (IOT_172); also elsewhere on the board
SD_DQ1: U11.114 (IOT_171); also elsewhere on the board
SD_DQ2: U11.113 (IOT_170); also elsewhere on the board
SD_DQ3: U11.110 (IOT_168); also elsewhere on the board
SD_DQ4: U11.106 (IOR_166); also elsewhere on the board
SD_DQ5: U11.102 (IOR_161); also elsewhere on the board
SD_DQ6: U11.99 (IOR_152); also elsewhere on the board
SD_DQ7: U11.96 (IOR_146); also elsewhere on the board
SD_DQ8: U11.95 (IOR_144); also elsewhere on the board
SD_DQ9: U11.97 (IOR_147); also elsewhere on the board
SD_DQ10: U11.98 (IOR_148); also elsewhere on the board
SD_DQ11: U11.101 (IOR_160); also elsewhere on the board
SD_DQ12: U11.104 (IOR_164); also elsewhere on the board
SD_DQ13: U11.105 (IOR_165); also elsewhere on the board
SD_DQ14: U11.107 (IOR_167); also elsewhere on the board
SD_DQ15: U11.112 (IOT_169); also elsewhere on the board
SD_LDQM: U11.94 (IOR_141_GBIN2); also elsewhere on the board
SD_RAS_N: U11.84 (IOR_120); also elsewhere on the board
SD_UDQM: U11.93 (IOR_140_GBIN3); also elsewhere on the board
SD_WE_N: U11.90 (IOR_138); also elsewhere on the board
VCCPLL0: C58.1, C59.1, R25.2, U11.54 (VCCPLL0)
VCCPLL1: C60.1, C61.1, R26.2, U11.126 (VCCPLL1)
